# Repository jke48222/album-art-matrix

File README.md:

# Album Art Matrix

A design for an LED wall that shows the cover of whatever song is playing, rendered as a slowly
spinning disc. Nine square LED panels tiled three by three, 480 mm on a side, driven by a Raspberry
Pi 5.

**No hardware has been driven yet.** Not nine panels, not one. This repository is the design, the
circuit simulation, and the software that will run on it. Some of the first light parts have since
been ordered; no panel has arrived. The section below is exact about what exists.

## Building it

[docs/ASSEMBLY.md](docs/ASSEMBLY.md) is the current guide: nine panels are
lit and mapped, and it takes them from the floor to a hung wall. The design
being built is in [design/](design/), the parts and prices at the end of
[PARTS.md](PARTS.md), and [docs/WALL-BUILD.md](docs/WALL-BUILD.md) is the
record of how the wiring was arrived at.

## Status

| Piece | State |
| --- | --- |
| Circuit simulation (`pcb/sims/`) | Done and reproducible. Eight ngspice decks, verified to regenerate their committed outputs bit for bit. |
| Backplane circuit (`pcb/circuit.py`) | Done as a netlist and BOM. 76 components, 105 nets, 345 pin connections. |
| PCB layout (`pcb/backplane.kicad_pcb`) | Routed. 20 design rule check runs are committed as `pcb/drc1.json` through `drc20.json`, and reading them in order is the honest record of the layout. The last run has **no rule violations and no unrouted signal**. What it still reports is 7 ground pour islands: the GND zone fragmented into pieces that no via stitches together, on a board whose entire power argument rests on a continuous return path. Its 107 warnings are 26 silkscreen clearances and, for the rest, KiCad noting that the vendored `pcb/footprints/` are not installed as a system library. |
| Fab outputs (`pcb/fab/`) | Gerbers, drill, pick and place, and board views are exported. **Stitch the ground islands before ordering.** |
| Art pipeline (`brain/art/`) | Built, runs on a laptop, has an offline test. |
| Wall control API (`brain/control.py`) | Built, 335 lines. Serves mode, brightness, spin rate, ambient settings, finishes, ticker and clock text, a sleep fade, a journal with replay, and raw frame and clip pushes on port 8788. Has run on the real Pi and answered the apps over the network; has never had a panel behind it. |
| Display modes (`brain/art/disc.py`, `effects.py`, `text_modes.py`) | Built. Spinning disc, eight ambient light effects (solid, breathe, pulse, rainbow, gradient, plaid, weave, deco), clock and ticker over a generated pixel font, plus pushed frames and clips. All verified as PNGs, none on an LED. |
| iOS companion, first app (`ios-companion/`) | Built, 4,406 lines of Swift. Reads the on device now playing state and pushes it to the reporter, and remote controls the wall. Runs on device. **The simulator cannot exercise it**, because MediaPlayer is stubbed there. Superseded by Tessera for daily use; still installs and works. |
| Tessera (`tessera/`) | The current iOS app. Three designs of the same room (a panel, an iPod with a click wheel, and a rendered room with a record player whose arm follows the song), Studio (draw, photo, words, video on one 64x64 canvas), Archive, Settings with every service set up from the phone, widgets and a Live Activity, an offline outbox, and a stand-in wall the phone runs when no hardware answers. The room's renders come from `tessera/Tools/room/room.py` (Blender, headless). The logo is the Record mark (`RecordMark.swift` and the icon) and the opening is its sting (`StingOpening.swift`: on black, or keyed over the room's light and then the room glitches in from coarse pixels; films `record-sting.mp4` and `record-sting-alpha.mov`, made by `Tools/record_sting.py` and a Higgsfield pass, see `Design/Logos/record/final/README.md`). The Room design is the default. Verified in the simulator against a local brain and installed on a phone; never against a panel. |
| Web app (`web/`) | Built and runs (TanStack Start + React). The whole pipeline reimplemented in TypeScript (Lanczos-3, Pillow-semantics unsharp, gamma 2.2, WB in linear light), plus a seven-source now-playing chain, an LED wall simulator, history, WB profiles, a wiring calculator, and push-to-wall. Verified live against `scripts/mac_reporter.py`; the brain push matches `brain/control.py`'s contract but has not been fired at the real Pi yet. |
| Panel intake QA (`scripts/panel_qa.py`) | Test pattern generator and procedure written, 271 reference frames rendered in `qa_preview/`. `qa/QA-SHEET.md` is an **empty template**. No panel has been through it. |
| Now playing, Apple Music (`brain/nowplaying/applemusic.py`, `applemusic_account.py`, `pushed.py`) | Built. On the Mac: the phone's push, then Music.app, then anything else the Mac plays (next row), then the account view through the MusicKit helper. On the Pi: the phone's push and the account view straight from MusicKit. The phone push and the Mac path have both answered live. |
| Now playing, anything the Mac plays (`brain/nowplaying/macmedia.py`) | Built. Reads macOS's own Now Playing through `media-control`, so Spotify's app, TIDAL, or a browser tab on YouTube Music, SoundCloud or Amazon Music reach the wall with their own artwork, which the reporter serves to the Pi. Verified live on this Mac: a YouTube Music tab reached the reporter with its title, progress and thumbnail, and the brain rendered it. |
| Now playing, Spotify (`brain/nowplaying/spotify.py`) | Built. The app id is pasted in Tessera and handed to the wall, the PKCE sign-in runs on the phone (`tessera://spotify`), and the wall polls from then on. Under the February 2026 rules the app id needs a Premium account, one client ID per developer and five users. **Not linked yet.** |
| Now playing, Last.fm and ListenBrainz (`lastfm.py`, `listenbrainz.py`) | Built. Last.fm needs an API key and a username; ListenBrainz needs only a username. Both are typed in Tessera and kept on the wall. Spotify, Tidal and Deezer report to Last.fm on their own; a browser scrobbler covers YouTube Music, SoundCloud and Amazon Music on a computer. **No account entered yet**, so neither has answered live. |
| Now playing, the wall's ears (`brain/nowplaying/ears.py`) | Built and proven on the Pi 2026-09-14: the USB microphone is read continuously, and when the room is louder than a gate the last few seconds are named through Shazam (shazamio; no key, but an unofficial client that Apple could break). Two six-second clips of quiet music matched in about two seconds each. AcoustID, the first attempt, was removed: it identifies whole files, not a room. Tessera's ears page shows the room's level live with the gate as a mark to drag, what was heard and where in the song, and the Hearing knobs. Handling for a noisy room (a longer clip after each miss, a named song kept through misses, a match with no catalogue record heard twice before it goes up) is built but not yet measured against a TV. |
| HomeKit (`brain/homekit.py`) | Built and running on the Pi 2026-09-15, not yet paired. One bridge: a light (on, off, brightness, a colour for the ambient face), a television (the faces as inputs, the Control Centre remote's keys), an occupancy sensor (sound in the room) and a motion sensor (music on the wall). The wall draws its pairing QR on the panel while unpaired; `GET /homekit` has the code as text. Siri, the Watch and scenes need nothing else; automations and a HomePod need a home hub. |
| Vinyl scrobbling (`brain/scrobble.py`) | Built 2026-09-15, running on the Pi, waiting for the ListenBrainz user token from the phone's ListenBrainz page. Every record the ear names is posted as playing-now, then as a listen after half the song or four minutes; held-through-noise and heard-again-within-the-song count once; listens the network refused wait in `scrobbles.jsonl` and go later in batches. Fifteen offline tests in `brain/tests/test_scrobble.py`. |
| Knock twice (`brain/nowplaying/knock.py`) | Built 2026-09-15, on the Pi, waiting for a session of real knocks to set the numbers. Two knocks on the frame, alone, toggle the wall between off and the face it had; a whistle bending up or down does the same for a frame that does not carry a knock. Both run on the ear's own chunks, log every candidate with its numbers, and are Hearing knobs on the phone. Fourteen offline tests. |
| Teach the wall a song (`brain/nowplaying/teach.py`) | Built 2026-09-15, on the Pi. The wall's own landmark fingerprint library (numpy, the Shazam idea; Olaf needs Zig, which the Pi's Debian lacks), asked before Shazam. It learns a song's iTunes preview when another source names it and the ear keeps missing it, learns the room's own hearing of a song after fifteen loud seconds, and learns by name through `POST /teach/learn`. Three Hearing knobs, a Taught songs group on the phone, nine offline tests including a clip heard through a room. |
| The wall's own ears, the voice (`brain/voice/`, `docs/VOICE.md`) | Built 2026-09-15. A wake word on the ear's stream, chosen on the phone from openWakeWord's Hey Jarvis, Hey Mycroft, Hey Marvin and Alexa, or a phrase of your own taught by saying it to the wall six times (matched on the same speech embeddings with the room's sound taken out; measured on synthetic voices, it heard 97% of new voices in an echoing room with no false wakes in 3.6 minutes of talk). Each word keeps its own sensitivity, with a live meter on the Voice page. Then the Horizon face while it listens, speech to text on the Pi (faster-whisper tiny, about a second and a half a sentence), a grammar of commands done with no cloud, and Claude for the rest. `GET /voice`, `GET /voice/meter`, `POST /voice/wakeword`, `POST /voice/enroll`, `POST /voice/wake` and `POST /voice/say` for testing without a microphone. |
| Ask the wall (`brain/ask.py`) | Built 2026-09-15, waiting for the Claude key from the phone's Services page. A question by voice or `POST /ask` goes to Claude Opus 5 with the wall's own tools (what is playing, the journal, the face, brightness, a timer) and comes back as words on the panel, paged, 1x at 64 and 2x at 192. A Siri Shortcut recipe is in `docs/ASK.md`. |
| Leave a note (`POST /note`, `docs/ASK.md`) | Built 2026-09-15. "Hey Siri, tell the wall back at six" runs the words across the panel for a while, then the wall goes back to what it was doing. Also a voice command. |
| Show me, play me, the earworm finder (`brain/show.py`) | Built 2026-09-15, pictures 2026-09-22. A picture of a thing by name (Google Images with a key and search engine set under Services, otherwise the web through DuckDuckGo's image search, then the lead image of its Wikipedia page, then Openverse) or a cover by name from iTunes into the frame face, a video by name through yt-dlp into the video face, and a song from the words remembered through Claude, with its sleeve. Plain words mean a picture unless they name a record the wall has worn or shelved; "cover", "album", "by" ask for a sleeve, "a picture of" asks for a picture. By voice or `POST /show` (with `kind`: picture, cover or any), `/play`, `/earworm`. |
| Weather faces (`brain/weather.py`, `brain/art/weather.py`) | Built 2026-09-15 and redrawn the same day at full fidelity, proven on the Pi with the real forecast for the room's place. A face that is the weather: a sky the colour of the hour (blue at noon, warm at the horizon at dawn and dusk, deep at night with stars that twinkle), rolling hills in silhouette, a sun with a halo and slow rays on its real arc, the moon with tonight's phase and its seas, clouds as stacked puffs with lit tops and shaded bases in two layers that drift, rain that leans with the wind and splashes on the ground, drizzle finer, showers that come and go, snow in two sizes banking up on the hills, fog as soft banks of haze drifting through, thunder with a forked bolt and a flash that fades; the temperature outlined so it reads over anything, at 192 the high and low, the next six hours and sunrise and sunset ticks where the arc meets the hills. Everything still for the hour is drawn once and kept. Every WMO code has a scene. Open-Meteo, no key; a place named once on the phone's Weather page, which is a card now: the wall's live frame, the temperature large, the sky in words, the day's range, feels, wind, sunrise, sunset and the next six hours. Seven tests. |
| The shelf (`brain/shelf.py`, `brain/art/mark.py`) | Built 2026-09-15, on the Pi, waiting for a Discogs token and username (Services > Discogs). The wall reads the collection's main folder every six hours, paced under Discogs's limit, and keeps it in `shelf.json`. A song from an album on the shelf gets a small record in the sleeve's corner, 5 px at 64 and 11 px at 192, dark on a light corner and light on a dark one, on every face that shows the sleeve; the Shelf knob turns it off. The pressing (year, label, catalogue number, country, the lowest price copies are going for) goes to the phone as `owned` and shows under the song; the price is fetched on a worker and cached a day. The Discogs page lists the shelf with plays per release from the journal. Matching folds case, accents, brackets, feat., Discogs's (2) and Deluxe tails, takes near titles (Blonde, Blond) and any listed artist, and prefers the vinyl. Seven tests over forty tricky releases. |
| Posters (`brain/posters.py`) | Built 2026-09-15, on the Pi, waiting for a TMDB key (Services > Posters) and for the Mac's reporter to be restarted from this tree. A show or a film in a browser on the Mac used to be dropped by the reporter (a browser icon is not a sleeve); now its name rides on the empty answer as an `X-Mac-Show` header, a brain that does not know about shows sees nothing new, and this brain looks the name up on The Movie Database, television first, then films. The poster is the sleeve, cut square from a little above the middle rather than squashed (`brain/art/pipeline.py` `square`, which now guards every non-square picture), the answer is playing with art, the journal marks it `kind: show`. Hits kept a month, misses a day, in `posters.json`. Six tests. |
| Imagine (`brain/imagine.py`) | Built 2026-09-15, drawing on the Pi with his OpenAI key. "Create a purple elephant", by voice or from the Imagine page: Claude rewrites the words as a prompt for one large, lit, textured, believable subject with no text; the newest OpenAI image model the key can reach draws it (gpt-image-2, then 1.5, then 1, with a fallback on a missing model) at medium quality to start (a good picture in well under a minute: 54 s for a lighthouse on gpt-image-2; high is the most detailed and takes minutes), or Google's Imagen Ultra. OpenAI streams three partial images and the wall shows the picture being drawn: the moment the words arrive it goes into its imagine face, a soft band of light sweeps across while the model thinks, each partial crossfades in as it lands, a line at the foot counts them, and the finished picture is held for ten minutes. Every image is brought to the wall's size in linear light with a gentle stretch. Kept at full size with its words in `imagined/`; `GET /imagine` lists them with the live state, `GET /imagine/<id>.png` serves one, `POST /imagine/show` puts one back with a quick reveal. AI pictionary shows its sketch forming the same way. The Imagine page shows the drawing live; Services > Images chooses the drawer and the quality. Ten tests. |
| AirPlay to the wall (`brain/nowplaying/airplay.py`, `brain/nowplaying/receiver.py`, `docs/AIRPLAY.md`) | Done 2026-09-15. The wall is an AirPlay speaker called Wall. `pi/install-airplay.sh` unpacks Debian's shairport-sync, a classic AirPlay build, so there is no nqptp and no root; the brain runs it with a config of its own, starts it again when it stops, restarts it when the phone renames it, and stops it with itself. A reader on its metadata pipe takes the title, artist, album, length, artwork, position, pause, resume, end and the sender, and answers right after the phone in the chain; a song that comes without artwork gets its sleeve by name. On the phone: whether it is receiving and from what, a switch, and the name. Proven on the Pi with an Apple device playing to it. Grouping with HomePods in the Home app needs AirPlay 2, which needs sudo. |
| Games shell and Wordle (`brain/games/`) | Built 2026-09-15 and played on the Pi over HTTP and by a spoken guess. One game at a time, held by the GameHost: mode `game`, the wall the board and the phone the hand; `GET /game/list`, `GET /game`, `POST /game/start`, `/game/move`, `/game/hear`, `/game/end`; every change bumps a sequence the phone polls; played, won, streak and best per player per game in `games.json`; a scoreboard face between games. Words heard by the wall's ears go to the running game before the command grammar. `brain/games/board.py` draws the same board at 64 and 192 from one description (tiles, grids, the 5x7 font at 1x and 3x). Word lists built from a public frequency list through the system dictionary: 30,000 common words, 2,400 five-letter answers, 8,500 valid guesses. Wordle: six guesses, the repeated-letter rule, a refused non-word does not count, the keyboard state for the phone, up to four players taking turns. Four tests. The phone's Games screen is next. |
| Sudoku, Spelling Bee, Letter Boxed, Connections (`brain/games/`) | Built 2026-09-15, each shown on the Pi. Sudoku: a full grid by randomised backtracking, digits removed while a counting solver still finds one solution, rated by the guesses that solver needs; easy, medium or hard; touch on the phone or "row three column four is seven"; wrong digits red. Spelling Bee: a hive from a common seven-letter pangram, the centre chosen to keep the most words, ranks from Beginner to Genius, Queen Bee for every word. Letter Boxed: two chaining common words that use twelve distinct letters and lay out on four sides with no two in a row from one side, kept as the par; the wall draws every word's lines. Connections: Claude writes a set (structured output) or one of eight bundled sets, yellow to purple, one away, four mistakes; say four words or tap four tiles. Fourteen tests. |
| Strands, mini crossword, Contexto, sliding puzzle, cover reveal, reaction knock, whistle bird (`brain/games/`) | Built 2026-09-15, each shown on the Pi. Strands: a themed set from Claude (structured output, forty-eight letters checked) or six bundled, threaded through the 6x8 grid by cutting a random whole-grid path (backbite moves on a serpentine) into the words, the spangram made to touch two sides; extras earn hints. Mini crossword: symmetric patterns filled from the common words most-constrained-slot first, Claude clues or a hand-clued puzzle, entered by voice ("one across is lamp") or a letter at a time, a check that marks wrongs red. Contexto: ranks by cosine on twenty thousand GloVe vectors cut to a 1.9 MB file, green under 300, the rank in big digits with a log bar. Sliding puzzle and cover reveal on a sleeve from the journal: a scramble by legal slides, blocks tapped or "up, down, left, right"; a Gaussian blur that sharpens over thirty seconds, first to name the album or artist. Reaction knock: red, green, the milliseconds on the panel, timed on the ear's own clock, false starts caught, phone taps allowed. Whistle bird: the ear's pitch, the whistler's range learnt in the first notes, pipes, a score. The ear now hands every lone knock, double, whistle and pitch to the running game first, so nothing switches the wall off mid-game. Twenty-three tests. |
| Heardle, pub quiz, twenty questions, AI pictionary, the arcade (`brain/games/`) | Built 2026-09-15. Heardle: a journal song with an iTunes preview the phone plays for one, two, four, seven, eleven, sixteen seconds as guesses miss or skip; the wall's six bars and a needle; the sleeve on the reveal. Pub quiz: a Claude round (structured output) or two bundled, twenty seconds a question, one answer per player, folded matching against every acceptable answer, scores on the wall. Twenty questions: Claude asks from the whole history and guesses when sure; a knock is yes, a whistle no; twenty and you win. AI pictionary: the image drawer draws a secret word from a list of drawable things with no text, sixty seconds to name it. The arcade: Pong (phones as paddles, the wall plays the other side alone, first to seven), Snake (a 32-cell grid, the phone the remote, or say the direction) and Tetris (a seven-piece bag, wall kicks, a ghost, levels). Eleven tests; the arcade shown on the Pi. |
| The Games sheet on the phone (`tessera/Tessera/Games.swift`, `GamesBoards.swift`, `GamesPlay.swift`) | Built 2026-09-15 and installed. A Games tile among the faces opens a sheet: the games the wall knows, your name for the scoreboard, the one that is on, its scores. Every game has its own screen polling the wall once a second and redrawing on its sequence: Wordle's rows and keyboard, Sudoku's grid and digit pad, Connections' tiles, the Spelling Bee hive, the Letter Boxed square, Strands traced by a finger, the mini crossword with its clues, Contexto's ranked list, Heardle playing the clip for the seconds allowed, the sliding blocks tapped over the wall's own frame, the reaction button, the whistle bird's slider, twenty questions' yes and no, the quiz card, pictionary's clock, Pong on the phone's tilt, Snake and Tetris on a remote and swipes. Words are typed or spoken to the phone's own recogniser, primed with the game's words. The state comes as JSON any game can shape. |
| The boards' design (`brain/games/board.py`, `scripts/render_games.py`) | Redrawn 2026-09-15 on one kit: a restrained palette, tiles with a lit top edge and a shaded bottom at 192 and their corners off at both sizes, hexagons, thick lines and arcs, soft glows, easing, a header band with a coloured mark at 192, a banner for the end of a game, a scoreboard with bars. Wordle's rows flip in a tile at a time, Connections shakes on a miss, Contexto pops its rank in, the quiz counts down on a ring, the reaction field breathes, the whistle bird flaps under stars, Pong's ball leaves a trail, Tetris has bevels, a ghost and a next piece. `scripts/render_games.py` draws every board at both sizes as one contact sheet. The phone's Games sheet has a hero card with the wall's live frame, a motif for every game in its colour, the scores as bars, and a live strip of the wall over each board. |
| Every feature in its place (`tessera/Tessera/Features.swift`, `brain/homekit.py`, `brain/art/horizon.py`, `brain/art/answer.py`) | 2026-09-15. Settings has a "What the wall can do" list: Ask the wall (a question typed, the answer on the panel or here, the last dozen), Notes (words on the panel for a set time, with what is up now), Show me (a cover or a video by name), Earworm (the words you remember, the sleeve with the name along its foot), Imagine, Weather, Games, Voice (the wake word and speech, listen now, say it from here, the last heard), HomeKit (pairing, the setup code on the panel, the remote's inputs), The shelf (the records as covers, most played first), Teach the wall (a song by name, the library). The HomeKit remote has every face as an input, the weather, the games and the last picture drawn among them; its arrows and select play a game that is on, back puts it down, play and pause switch the wall off and on. The listening line ripples along its length with the voice and glows under it; the thinking bead trails light; answers type themselves out with a cursor. An organisation-level Claude key now works: the wall sends the workspace id set beside it. |
| Service settings from the phone (`brain/services.py`, `tessera/Tessera/Services.swift`) | Built and exercised against a brain on the Mac: every key and username above is set from Tessera's Services pages, kept in `services.json` on the wall, and applied to the running adapters without a restart. No config file is edited by hand once the wall is deployed. |
| Video on the wall (`brain/video/`, `tessera/Tessera/Video.swift`, `VIDEO.md`) | Built and exercised on the Pi 2026-09-06. A YouTube link (or any link ffmpeg reads) pasted in Tessera's Video face: the wall resolves it the way the YouTube iPhone app does, streams the 144p picture through ffmpeg to 64 px at 15 fps (a third of a second of CPU per twenty seconds of video, about 26 MB of frames), and downloads the sound in ranged pieces for the phone to play; the phone's player is the clock. First frame in about a second, sound ready in under two. No new binaries on the Pi. Share-sheet target (`tessera/TesseraShare/`): from YouTube, Safari or Photos, Share, then Tessera; a library video is sent up as a small H.264 picture (`POST /video/upload`) and the phone plays its own sound. Videos behind YouTube's signed-in token (big label releases) stop after the first megabyte from every client identity the wall asks; those fall through to **yt-dlp** (`brain/video/ytdlp.py`, installed by `pi/install-ytdlp.sh`), which fetches them itself into the RAM disk. Verified on the Mac 2026-09-06: the refused video plays, ready in 7.3 s against 1.8 s for the fast path. No JavaScript runtime installed; not needed by the client yt-dlp uses. |
| Renderer (`renderer/art_display.c`) | 202 lines of C. Compiled and run on the Pi 5; frames flow through the FIFO and the map-rate cap. It has never had a panel on the other side. |
| Pi provisioning (`pi/`) | Executed on the real Pi: bootstrap, venv, renderer build, systemd units for brain and renderer. The wall boots headless and answers the network. |
| Parts | **Panels arrived**: ten Waveshare P2.5 64x64, driver confirmed FM6124HJ (conventional, no init sequence needed). Pi 5, card, cooler and sundries on hand. First light is blocked on the HUB75 bonnet and 5V supplies still on order. `PARTS-TRACKER.xlsx` carries prices actually paid; `PARTS.md` remains the list. |
| White balance gains | Placeholders. `config.example.toml` labels the current values "a GUESS" pending measurement. |

Everything above is design, simulation, and software. Nothing in this repository has met a panel,
and that is the only claim that matters until it changes.

## What problem this solves

Music has a cover, and almost nobody looks at it any more. It lives in a thumbnail the size of a
postage stamp, at the corner of a phone that is in a pocket. The cover is the one piece of visual art
that shipped with the record, and the streaming era has quietly retired it.

An LED matrix wall puts it back on the wall at the size it deserves, and makes it live: it changes
when the song changes, without anyone touching anything.

The obvious approach, a cheap TV showing a full screen image, fails for a specific reason. A TV in a
room reads as a switched-on screen. It has a bezel, a backlight glow, an off state that is a grey
rectangle. An LED matrix behind a diffuser reads as an object that emits light, closer to a lamp or a
sign than a display, and its off state is genuinely black. That difference is the entire point of
building the hard version.

## What HUB75 is

HUB75 is the de facto wiring standard for chainable RGB LED matrix panels. A 16 pin ribbon carries
six colour data lines (two sets of red, green, blue, because the panel drives two rows at once), five
row address lines named A through E, a clock, a latch, and an output enable.

The important thing about HUB75 is what it does **not** have: memory, or brightness control, or any
intelligence at all. The panel is a shift register attached to LEDs. It displays exactly one row pair
at a time, and it stays lit only for as long as you hold output enable low. To make a picture, the
host has to scan every row of the panel, over and over, fast enough that persistence of vision fuses
the rows into an image, and it has to modulate the on time of each row to produce anything other than
full brightness. If the host stops, the image does not freeze. It goes dark.

That is why this project needs a real time thread pinned to a dedicated CPU core, and why the signal
integrity of a 25 MHz clock down a ribbon cable is a design problem rather than a detail.

## How it works

```
  Mac                          Pi 5
  ---                          ----
  Music.app ---+
               +--> mac_reporter.py --HTTP--> brain/main.py
  MusicKit  ---+   (port 8787)                     |
  helper                                           | poll, detect track change
                                                   v
                                          art/fetch.py
                                          cover URL to cached image
                                                   |
                                                   v
                                          art/pipeline.py
                                          Lanczos downscale, unsharp, sRGB to
                                          linear, white balance, re-encode
                                                   |
                                                   v
                                          sinks/pi_renderer.py
                                          one RGB888 frame per open/write/close
                                                   |
                                                   v
                                          /tmp/album-frame.fifo  (named pipe)
                                                   |
                                                   v
                                          renderer/art_display  (C daemon)
                                          reader thread, plus a refresh thread
                                          pinned to isolated CPU 3
                                                   |
                                                   v
                                          HUB75 ribbon --> LED panels
```

The seam worth noticing is the named pipe. The brain and the renderer are separate processes that
share nothing but a byte stream of raw pixels, so either can be restarted, replaced, or run under a
debugger without the other caring. `art_display` re-opens the pipe on end of file and keeps showing
the last frame it received, so a crashed or upgraded brain leaves the wall lit rather than black.

On a laptop, `sinks/mac_preview.py` swaps in for the pipe and writes a scaled up PNG with a pixel
grid instead. That is how the whole image path was developed with no panel in the room.

## The simulations

This is the part of the project that is fully substantiated, and it is the part worth reading.

`pcb/sims/run_sims.py` writes ngspice decks, shells out to `ngspice -b`, and plots the results. Five
deck templates produce eight numeric output files and three figures, all committed. I re-ran all
eight decks from the committed `.cir` files and compared against the committed `.txt` outputs: every
one matches bit for bit, so the numbers below are reproducible rather than remembered.

Read them as circuit models, not as measurements. Nothing here has been checked against a real board,
because there is no real board.

### Why HUB75 lines need series termination

A logic driver puts out a fast edge. A 30 cm ribbon cable is not a wire, it is a transmission line
with inductance and capacitance distributed along it, and the panel at the far end is a high
impedance input that reflects almost all of the energy that arrives back toward the driver. The
reflection returns, bounces off the driver, and comes back again. What you see at the panel is
ringing: the voltage overshoots well past the supply rail, undershoots below ground, and settles only
after several round trips.

Series termination is the cheap fix. Put a resistor in line at the driver so that the driver's output
impedance plus the resistor roughly matches the cable's characteristic impedance. The reflection that
comes back is then absorbed instead of re-launched.

The sweep drives a 25 MHz pulse through an 18 ohm source resistance and a six section lumped LC
ladder standing in for the ribbon (25 nH and 2.5 pF per section), into an 18 pF panel input.

| Series resistor | Peak at panel input | Worst undershoot |
| --- | --- | --- |
| 0.1 ohm (effectively none) | 8.71 V | -4.11 V |
| 22 ohm | 7.09 V | -2.13 V |
| **33 ohm** | **6.48 V** | **-1.49 V** |
| 47 ohm | 5.86 V | -0.86 V |

Undamped, a 5 V signal swings to 8.7 V and to -4.1 V. Those excursions are what the panel driver
chip's input protection diodes have to eat, on every clock edge, forever.

47 ohm damps hardest, but it also slows the edge, and at 25 MHz the edge is a large fraction of the
bit period. 33 ohm is the value in `pcb/DESIGN.md`, chosen from this sweep as the point where
overshoot is tamed without blunting the edge. One caveat this figure carries in its own legend: the
plot says "Rs = 0" for the first trace because the script formats the label with `int(rs)`, while the
deck actually uses 0.1 ohm.

### What IR drop costs across the power distribution

An LED panel at full white is a serious load. One 64 by 64 P2.5 panel pulls roughly 4 A, so a section
of three panels pulls about 12 A. Copper has resistance, and 12 A through even a short run of 14 AWG
wire, a fuse, fuse clips, and a panel harness adds up to a voltage that is missing by the time it
reaches the panel. That is IR drop: current times resistance, the voltage the wiring keeps for
itself.

It matters because these panels are not tolerant. Below roughly 4.9 V the driver chips start
misbehaving, and the symptom is not a clean failure. It is dim patches, colour shifts on bright
frames, and flickering that only appears on white heavy album covers.

The deck is a DC sweep of the supply's output trim, with three constant current loads of 4 A each,
through modelled trunk wire, 7 milliohm of fuse and clips, and 0.4 m of 18 AWG harness per panel.

| Trunk length | Panel voltage at 5.00 V trim | Trim needed for 5.00 V at the panel |
| --- | --- | --- |
| 1.0 m of 14 AWG | 4.71 V | about 5.30 V |
| 0.5 m of 14 AWG | 4.81 V | about 5.20 V |

So a supply set to a perfect 5.00 V delivers 4.71 V to the panel, below the floor, and the wall
misbehaves on bright frames for reasons that look like a software bug. The answer is not thicker wire
alone, it is to trim the supply up so the panel lands in range, and the sweep says exactly how far.
Halving the trunk length is worth 0.10 V, which is why the design splits the wall into three
independent 12 A sections instead of running one 36 A trunk.

### Why inrush limiting matters

A switching power supply has a large capacitor across its input. At the instant you plug it in, that
capacitor is empty, and an empty capacitor looks like a short circuit. The only thing limiting the
current is the resistance of the mains wiring and the capacitor's own equivalent series resistance,
which together are a fraction of an ohm.

The deck models the first few AC cycles into roughly 560 uF of input bulk, at the worst case moment
of connection (the peak of the mains sine wave).

| Configuration | Peak line current |
| --- | --- |
| No limiter | 275 A |
| SL22 NTC thermistor, 10 ohm cold | 15.8 A |

275 A is a number that trips breakers, welds switch contacts, and shortens the life of everything it
passes through. The fix is a negative temperature coefficient thermistor in the mains line: cold, it
is 10 ohm and limits the surge to 16 A, and then it self heats within a second or two down to a
fraction of an ohm so it costs almost nothing during normal running. This is why an SL22 10005 is on
the Mouser line of `PARTS.md` and why the design puts it in the AC line rather than anywhere on the
board.

The model uses a generic diode bridge and a fixed cold resistance with no self heating, so it is
honest about the first cycle and says nothing about the settled behaviour.

## The board, written as a Python program

`pcb/circuit.py` is 207 lines that describe the backplane as data and emit it. Running it prints a
connectivity report and writes `backplane.net` (a KiCad netlist) and `bom.csv`. I ran it into a
scratch directory and diffed: both outputs regenerate identically to the committed files.

```
parts: 76   nets: 105   pin connections: 345
single-node nets (should be none): none
GPIOs consumed: [2, 3, 4, ..., 27]
```

The reason to do it this way instead of drawing a schematic is that most of this board is repetition
with an index. Three chains, nine panel drops, three power sections, twenty six buffered GPIO lines
each needing a series resistor from a shared pool of arrays. In a schematic editor that is a lot of
careful copying, and copying is where wiring errors come from. As a loop it is four lines, and the
pin map is stated once:

```python
SHARED = {"CLK": 17, "LAT": 4, "OE": 18, "A": 22, "B": 23, "C": 24, "D": 25, "E": 15}
CHAIN = {1: {"R1": 11, "G1": 27, "B1": 7, "R2": 8, "G2": 9, "B2": 10}, ...}
```

The script also checks itself. It reports any net with fewer than two nodes, which catches the most
common data entry mistake (a pin connected to nothing), and it prints which GPIOs the design consumes
so the fact that this pinout uses every one of BCM 2 through 27 is visible rather than discovered
later.

What this is not: a board. A netlist says what connects to what. It says nothing about whether the
parts fit in 170 by 110 mm, whether the 12 A pours are wide enough, or whether the layout passes a
manufacturer's design rules. That work is listed as the next step at the bottom of `pcb/DESIGN.md`
and has not been done.

## The render path

`renderer/art_display.c` creates the named pipe, holds it open, and streams frames out of it back
to back. It does not hand the brain's bytes to the panel library as they are: it keeps the last frame
received and, once per scanned frame, draws it again with temporal dithering, a running fraction per
LED colour, so a pixel can show a fraction of one of the library's 64 brightness slots and a dark
brown stops breaking into a lone red LED. The library bakes its brightness cap into a table once at
launch, so the renderer applies the cap itself, live, from each frame's header. It maps exactly once
per scanned frame by waiting on a swap counter that `pi/hub75-swap-counter.py` adds to the library;
before that counter the safe rate was 60 Hz and anything faster tore. The main thread calls
`render_forever()`, which owns the refresh loop.

It compiles and runs on the Pi 5. It includes `<rpihub75/rpihub75.h>` and links `-lrpihub75_gpu`,
the third party library `bitslip6/rpi-gpu-hub75-matrix`, which `pi/bootstrap.sh` clones and builds;
that has all run on the real Pi. What has not happened is a panel: the renderer's output has only
ever gone into the library, never into LEDs.

One number needs a label. The comment in `art_display.c` and the comment in `pi/run_renderer.sh` both
mention 9600 Hz. **That is the refresh rate advertised by that third party library, on hardware this
project does not own.** It is a design target that motivates the architecture (a refresh that fast is
what makes the wall photograph without banding, and what makes a torn frame invisible), and it is not
a measurement. Nothing in this repository has measured a refresh rate.

Likewise, `pi/run_renderer.sh` passes `-p 1 -c 1 -x 64 -y 64`: one port, one chain, one 64 by 64
panel. `config.example.toml` says the same thing in a comment: "S1: one 64x64 P2.5 panel. Later: 128
(4 panels) / 192 (9)". The nine panel wall is the plan. The configured system is one panel.

## CPU isolation

`pi/bootstrap.sh` appends `isolcpus=3 nohz_full=3` to the Pi's kernel command line. Two settings,
both about getting the Linux scheduler out of the way:

- `isolcpus=3` removes core 3 from the scheduler's general pool. Ordinary threads will not be placed
  there, so a thread that pins itself to core 3 has the core to itself.
- `nohz_full=3` stops the periodic timer interrupt on that core when only one thread is runnable on
  it. Without it, the kernel interrupts the core hundreds of times a second just to keep time.

The reason this is worth doing is in how HUB75 works, above. The refresh thread is not rendering
frames, it is bit banging a scan: hold a row's data on the bus, pulse the clock, latch, hold output
enable low for a precisely timed interval, repeat. The interval is what encodes brightness. If the
scheduler preempts that thread mid interval, the row stays lit longer than intended, and the result
is a visible bright line or a flicker in what should be a still image. A dropped frame in a video
game is a stutter you forgive. A late microsecond here is a defect on a wall you are staring at.

This is configured, not demonstrated. The line is in the script, the script has never run, and no
latency has been measured.

## Colour, and the number that is still a guess

The pipeline in `brain/art/pipeline.py` does white balance the correct way, which is the one part of
the image path with a real argument behind it.

RGB LED panels are not neutral. Their green and blue emitters are typically far more efficient than
their red, so a frame that says "white" comes out cyan. The correction is per channel gains. The
subtlety is *where* you apply them: an 8 bit image is gamma encoded, not linear, so scaling those
values directly scales perceptual codes rather than light. The pipeline decodes to linear light
(gamma 2.2), applies the gains there, clips, and re-encodes:

```python
linear = np.power(arr, 2.2)
linear *= np.asarray(gains, dtype=np.float32)[None, None, :]
np.clip(linear, 0.0, 1.0, out=linear)
encoded = np.power(linear, 1.0 / 2.2) * 255.0
```

The gains themselves are R 1.00, G 0.75, B 0.55, and `config.example.toml` labels them exactly as
they should be labelled:

> these starting gains are the research's typical values, a GUESS.

They are a starting point from published typical values, not a measurement of any panel. Measuring
them is a written procedure that has not been carried out: `scripts/WB-PROCEDURE.md` calls for a
TCS34725 colour sensor on a Pico 2 W (`scripts/pico_colorimeter.py`) held against a panel showing
full white (`scripts/show_white.py`), after a ten minute warm up because LED output shifts as the
panel heats.

## Running the software with no hardware

Requires Python 3.11 or newer (the config loader uses `tomllib`).

```bash
python3 -m venv .venv
.venv/bin/pip install -r brain/requirements.txt   # requests, Pillow, numpy
cp config.example.toml config.toml
```

The offline test needs no network, no accounts, and no panel. It synthesizes a 640 by 640 cover
containing a smooth gradient, a disc, and fine detail, chosen to expose banding, aliasing, and
downscale mush respectively, then runs the full art pipeline:

```bash
.venv/bin/python scripts/smoke_test.py
```

A successful run prints `smoke test OK:` and writes three files:

| File | What it shows |
| --- | --- |
| `preview_out/smoke_source.png` | The synthetic source cover |
| `preview_out/panel.png` | 64 by 64, scaled up with hard pixel edges and a grid, as the wall would show it |
| `preview_out/wb_compare.png` | Side by side, without and with the white balance step |

`wb_compare.png` will look wrong on a monitor, and that is the point. White balance compensates for
panel hardware, so on a correctly behaved screen the corrected version looks orange.

To run the live loop against Apple Music on a Mac:

```bash
.venv/bin/python -m brain.main --config config.toml
```

It polls every 5 seconds and rewrites `preview_out/panel.png` on each track change. Two caveats. The
Apple Music adapter's highest tier shells out to a MusicKit helper at
`~/.config/widgetsuite/musickit-fetch.py`, which lives outside this repository and is not verified
here; its lower tier uses `osascript` against Music.app, which triggers a one time macOS automation
prompt. Add `--once` to poll a single time and exit.

To have the Mac report every other app it plays as well (Spotify's app, TIDAL, a browser tab on
YouTube Music), install `media-control` once; both the brain on a Mac and `scripts/mac_reporter.py`
pick it up on their next start, with no setting to flip:

```bash
brew install media-control
```

Connecting a service needs no computer at all. Tessera's Settings > Services pages take the Spotify
app id, the Last.fm key and username and the ListenBrainz username, hand them to
the wall (`POST /services`), and the wall keeps them in `~/.config/album-art-matrix/services.json`
and starts using them at once. The Spotify sign-in itself runs on the phone. The values in
`config.toml` are only seeds; anything set from the phone wins. What still needs a computer is the
one-time `./deploy.sh` that puts the software on the Pi.

The developer's own keys live in `tessera/Tessera/DeveloperKeys.swift`. Only what is safe to
publish goes in there, because this repository is public. The Spotify app id qualifies: it is public
by design, the way every app with a "Sign in with Spotify" button was registered once by its
developer, and the sign-in uses PKCE so there is no secret to keep. A **Last.fm API key does not**:
it is bound to the developer's Last.fm account and a published one can be copied and revoked for
someone else's abuse, so that field is empty and the key is typed into Tessera's Services page
instead, which keeps it in `services.json` on the wall. With a key filled in, the app hands it to
any wall it meets that is missing one, and a person only ever signs in to Spotify or types a
Last.fm or ListenBrainz username. With it empty, the Services pages walk through making it by hand.

To re-run the circuit simulations, you need `ngspice` on your PATH plus numpy and matplotlib:

```bash
python3 pcb/sims/run_sims.py    # rewrites the .txt data and the three PNGs
python3 pcb/circuit.py          # rewrites backplane.net and bom.csv
```

## First light, when the parts arrive

The order of operations in `pi/PI-SETUP.md`, which is a runbook whose third step literally begins
"Pi arrives". Nothing below has been done.

1. Flash Raspberry Pi OS Lite 64 bit, hostname `album-matrix`, user `pi`, SSH key configured.
2. `./deploy.sh --bootstrap`, which rsyncs the source and remotely runs `pi/bootstrap.sh`: apt
   dependencies, zram, clone and build the panel library, append the CPU isolation flags, build the
   renderer, create the venv, install the systemd unit (not enabled).
3. Reboot, so the kernel command line change takes effect.
4. Wire it with everything unplugged. Ribbon into the panel's INPUT connector, panel power from its
   own supply, never from the Pi. Mains into the supply last.
5. Start `pi/run_renderer.sh` in one shell and the brain in another, with `[sink] type = "pi"` and
   the reporter endpoint pointed at the Mac.
6. Warm up ten minutes, then run the white balance procedure and replace the guessed gains with
   measured ones.

The first honest checkpoint is the one `pi/PI-SETUP.md` names: a photograph of the panel next to the
same cover on a phone, with the two colours matching. Until that photo exists, this project has not
displayed anything.

## Project layout

```
brain/                  4238 lines of Python: the now playing control plane
├── main.py             Poll loop, render loop, journal writes. A dirty event
│                       from the API wakes it instead of waiting out the poll.
├── services.py         Keys and usernames the phone hands the wall; kept in
│                       services.json, applied to the adapters live
├── control.py          HTTP state API on 8788. Mode, brightness, spin rate,
│                       ambient, finishes, ticker and clock, sleep fade,
│                       journal + replay, raw frame and clip pushes. State
│                       persists to control.json; plays go to journal.jsonl.
├── nowplaying/
│   ├── pushed.py       What the phone posts straight to the wall
│   ├── applemusic.py   Tiered: a state file, Music.app over osascript, any
│   │                   other app the Mac plays (macmedia), the account view
│   ├── applemusic_account.py  The account view from the Pi, no Mac in the path
│   ├── macmedia.py     macOS Now Playing via media-control: Spotify's app,
│   │                   TIDAL, browser tabs, with their artwork
│   ├── spotify.py      PKCE OAuth from the phone or a Mac; the wall polls
│   ├── lastfm.py       One account Spotify, Tidal and Deezer report to
│   ├── listenbrainz.py The open ledger; reading it needs no key
│   └── ears.py         The wall's microphone, read all the time; Shazam names it
├── art/
│   ├── fetch.py        Cover URL to cached image (decode before cache)
│   ├── pipeline.py     The colour work
│   ├── disc.py         Sleeve as a spinning disc, supersampled, fixed sheen
│   ├── effects.py      Eight ambient generators for when nothing is playing
│   ├── pixelfont.py    The 5x7 font, single source for both apps' Swift copies
│   └── text_modes.py   Clock and scrolling ticker over that font
└── sinks/              mac_preview.py (PNG, for development), pi_renderer.py (FIFO)

ios-companion/          AlbumWall, the first app, 4,406 lines of Swift
├── AlbumWall/          The app: on device now playing push, wall remote,
│                       photo and video push, App Intents, Live Activity
├── AlbumWallWidgets/   Home screen widgets and the Live Activity surface
└── design/             Screen designs the app was built from

tessera/                The current iOS app, 26,472 lines of Swift
├── Tessera/            Wall screen, Studio (draw / photo / words / video),
│                       Archive, Settings, offline outbox, stand-in wall
├── TesseraWidgets/     Home screen widgets
├── Shared/             Live Activity attributes, shared snapshot
└── Tools/              gen_pixelfont.py (regenerates both apps' fonts),
                        make_icon.py

web/                    The control plane in a browser: pipeline (same math,
                        TypeScript), source chain, wall simulator, history,
                        WB profiles, power model, push to the Pi brain.
                        `cd web && npm install && npm run dev`. See web/README.md.

pcb/
├── DESIGN.md           The backplane's rationale, signal design, power design, costs
├── circuit.py          The circuit as data. Emits the two files below.
├── backplane.net       Generated KiCad netlist, 76 parts, 105 nets
├── bom.csv             Generated bill of materials
├── layout.py           Placement, driving the KiCad board file
├── backplane.kicad_pcb The board. Routed; 7 ground pour islands left to stitch.
├── drc*.json           20 design rule check runs, in order. The trend is the story.
├── footprints/         Vendored .kicad_mod files, so the board opens anywhere
├── fab/                Gerbers, drill, pick and place, board views
└── sims/               ngspice decks, numeric outputs, three figures, run_sims.py

renderer/               art_display.c (202 lines) and its Makefile. Builds and
                        runs on the Pi; no panel has been on the other side.
pi/                     PI-SETUP.md runbook, wiring.svg, bootstrap.sh, run_renderer.sh,
                        systemd units
scripts/                mac_reporter.py (Mac HTTP endpoint the Pi polls), panel_qa.py +
                        PANEL-INTAKE.md (per panel intake), spin_demo.py, gen_tracker.py,
                        smoke_test.py, show_white.py, pico_colorimeter.py, WB-PROCEDURE.md
qa_preview/             271 rendered QA patterns
qa/QA-SHEET.md          Per panel results. Empty; no panel has been tested.
PARTS.md                Shopping list. Prices checked 2026-08-19.
PARTS-TRACKER.xlsx      What was actually ordered, and what it cost
config.example.toml     Copy to config.toml
deploy.sh               rsync to the Pi, with --bootstrap for the first run
```

## What is not built

Stated plainly, because the value of everything above depends on this list being complete.

- **No panel has been driven.** The ten panels have arrived and the Pi runs the whole software
  stack, but the bonnet and the 5V supplies have not landed, so nothing in this repository has lit
  an LED.
- **The PCB is routed but not signed off.** The last design rule check finds no violations and no
  unrouted signal, but it still reports 7 ground pour islands, which is the one defect that matters
  most on a board whose power design assumes a continuous return. Gerbers exist; stitch the ground
  first. The board is also still parked: the build uses the bonnet and bus bar path.
- **Neither iOS app's now playing path is verifiable off a phone.** They build and run on device,
  but the simulator stubs MediaPlayer, so that path is only ever exercised on real hardware.
- **No panel has been through intake QA.** The patterns and the procedure exist; the results sheet
  is an empty table.
- **The renderer's output has never reached an LED.** It compiles and runs on the Pi, but with no
  panel attached everything it maps goes into the library and stops there.
- **No streaming account is linked yet.** The Spotify, Last.fm and ListenBrainz
  adapters are written, but every credential in `config.toml` is still empty, so none of them has
  answered live. Only Apple Music (phone push, Music.app, account view) and the Mac's own Now
  Playing have.
- **Nothing on an iPhone other than Apple Music can be read by an app.** iOS gives an app only the
  Music player; Spotify, Tidal and Deezer reach the wall through their own accounts (Spotify's
  API, or Last.fm), and SoundCloud, YouTube Music and Amazon Music reach it only from a Mac or
  out loud.
- **Panel performance is unmeasured.** The software side is measured (`scripts/bench_frames.py`
  bounds the producer, the brain prints its sustained fps, and the 60 Hz map cap came out of a
  measured black-flashing regression), but refresh on real LEDs, CPU under a real load, and power
  draw are not. The 9600 Hz figure in the source comments is the panel library's specification,
  not a result from this room.
- **History is a journal, not a database.** Plays land in `journal.jsonl` (capped at 500, replay
  by timestamp); there is no search and no analytics on the brain side.
- **Every app is unproven against a wall.** Web, AlbumWall and Tessera all drive
  `brain/control.py`, and that API has run on the real Pi, but the loop from app to brain to lit
  panel has never been closed.
- **The web app's push-to-wall has not touched the Pi.** Its "Pi brain" push format matches
  `brain/control.py`'s `/frame` contract byte for byte, and the CORS headers that let a browser call
  that API are committed here, but the Pi was offline when this landed, so the loop web → brain →
  panel has never been closed. The Apple Music bridge path, by contrast, was verified live.
- **The white balance gains are unmeasured**, and labelled as such in the config.
- **No automated tests.** `scripts/smoke_test.py` is a visual check that writes PNGs for a human to
  look at, plus one assertion on frame size. There is no test runner and no CI.

---

Jalen Edusei, [jalenedusei.com](https://www.jalenedusei.com),
[github.com/jke48222](https://github.com/jke48222)

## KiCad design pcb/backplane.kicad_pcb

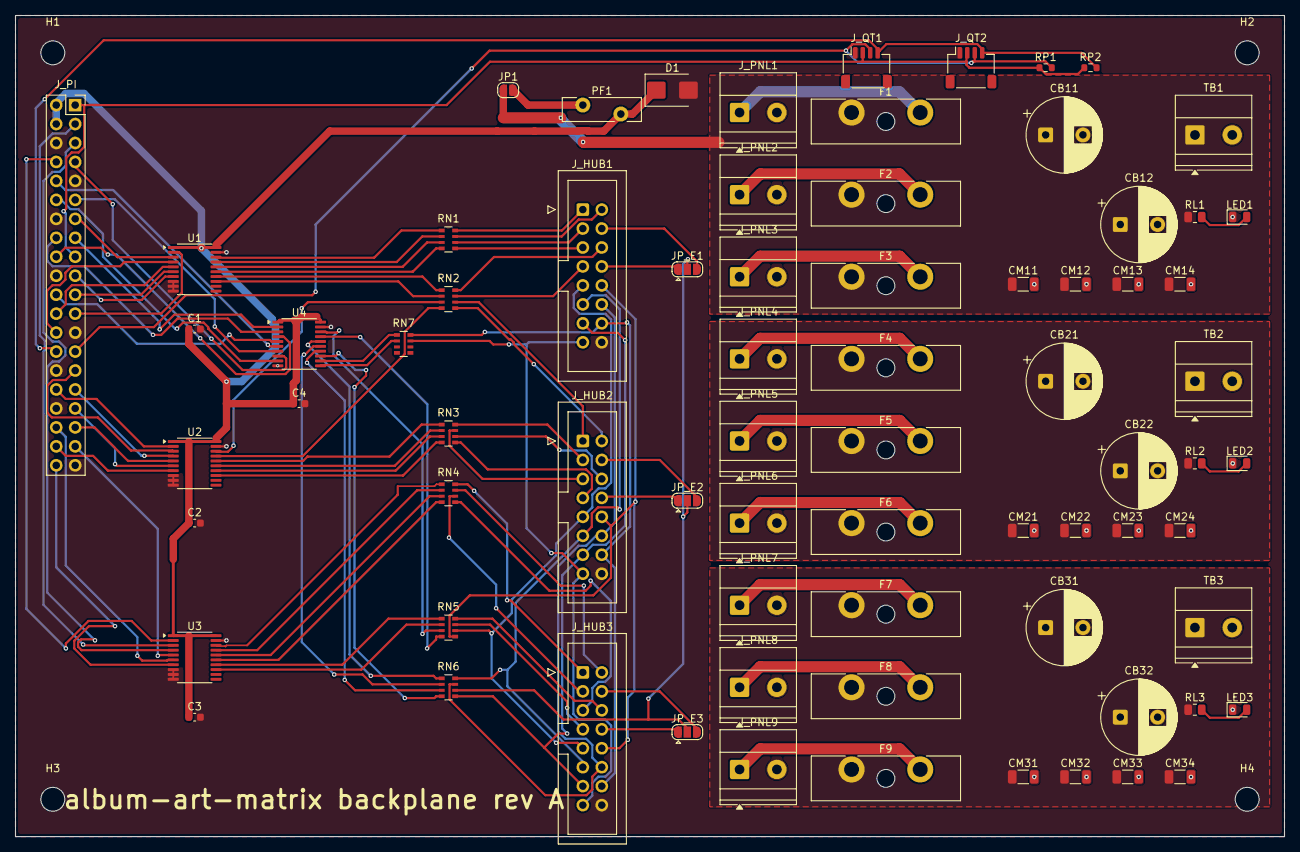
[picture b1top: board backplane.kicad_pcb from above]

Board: 2 copper layers, 170.0 x 110.0 mm, 78 parts (0 on the bottom side), 105 nets.

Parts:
C1, C2, C3, C4: 100nF; C_0603_1608Metric
CB11, CB12, CB21, CB22, CB31, CB32: 1000uF_10V; CP_Radial_D10.0mm_P5.00mm
CM11, CM12, CM13, CM14, CM21, CM22, CM23, CM24, CM31, CM32, CM33, CM34: 22uF_10V; C_1206_3216Metric
D1: SMBJ5.0A; D_SMB
F1, F2, F3, F4, F5, F6, F7, F8, F9: ATO_FUSE_10A; Fuseholder_Blade_ATO_Littelfuse_Pudenz_2_Pin
H1, H2, H3, H4: M3; MountingHole_3.2mm_M3
JP1: PI_PWR_EN; SolderJumper-2_P1.3mm_Open_RoundedPad1.0x1.5mm
JP_E1, JP_E2, JP_E3: E_PIN8_or_PIN4; SolderJumper-3_P1.3mm_Open_RoundedPad1.0x1.5mm
J_HUB1, J_HUB2, J_HUB3: HUB75_IDC_2x8; IDC-Header_2x08_P2.54mm_Vertical
J_PI: PI5_GPIO_2x20; PinSocket_2x20_P2.54mm_Vertical
J_PNL1, J_PNL2, J_PNL3, J_PNL4, J_PNL5, J_PNL6, J_PNL7, J_PNL8, J_PNL9: PANEL_5V_OUT; TerminalBlock_Phoenix_MKDS-1,5-2_1x02_P5.00mm_Horizontal
J_QT1, J_QT2: STEMMAQT_I2C0; JST_SH_SM04B-SRSS-TB_1x04-1MP_P1.00mm_Horizontal
LED1, LED2, LED3: PWR_GREEN; LED_0805_2012Metric
PF1: POLYFUSE_5A; Fuse_Bourns_MF-RG500
RL1, RL2, RL3: 1k; R_0805_2012Metric
RN1, RN2, RN3, RN4, RN5, RN6, RN7: 33Rx4; R_Array_Convex_4x0603
RP1, RP2: 10k; R_0603_1608Metric
TB1, TB2, TB3: TRUNK_IN_12A; TerminalBlock_Phoenix_MKDS-1,5-2_1x02_P5.00mm_Horizontal
U1, U2, U3, U4: 74AHCT245PW; TSSOP-20_4.4x6.5mm_P0.65mm

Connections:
3V3: J_PI.1, J_PI.17, J_QT1.2, J_QT2.2, RP1.1, RP2.1
GND: C1.2, C2.2, C3.2, C4.2, CB11.2, CB12.2, CB21.2, CB22.2, CB31.2, CB32.2, CM11.2, CM12.2, CM13.2, CM14.2, CM21.2, CM22.2, CM23.2, CM24.2, CM31.2, CM32.2, CM33.2, CM34.2, D1.2, J_HUB1.16, J_HUB2.16, J_HUB3.16, J_PI.6, J_PI.9, J_PI.14, J_PI.20, J_PI.25, J_PI.30, J_PI.34, J_PI.39, J_PNL1.2, J_PNL2.2, J_PNL3.2, J_PNL4.2, J_PNL5.2, J_PNL6.2, J_PNL7.2, J_PNL8.2, J_PNL9.2, J_QT1.1, J_QT2.1, LED1.1, LED2.1, LED3.1, TB1.2, TB2.2, TB3.2, U1.8, U1.9, U1.10, U1.19, U2.8, U2.9, U2.10, U2.19, U3.8, U3.9, U3.10, U3.19, U4.10, U4.19
GPIO2: J_PI.3, U3.3
GPIO3: J_PI.5, U3.4
GPIO4: J_PI.7, U4.8
GPIO5: J_PI.29, U2.3
GPIO6: J_PI.31, U2.4
GPIO7: J_PI.26, U1.4
GPIO8: J_PI.24, U1.5
GPIO9: J_PI.21, U1.6
GPIO10: J_PI.19, U1.7
GPIO11: J_PI.23, U1.2
GPIO12: J_PI.32, U2.2
GPIO13: J_PI.33, U2.6
GPIO14: J_PI.8, U3.2
GPIO15: J_PI.10, U4.6
GPIO16: J_PI.36, U3.6
GPIO17: J_PI.11, U4.7
GPIO18: J_PI.12, U4.9
GPIO19: J_PI.35, U2.5
GPIO20: J_PI.38, U2.7
GPIO21: J_PI.40, U3.7
GPIO22: J_PI.15, U4.2
GPIO23: J_PI.16, U4.3
GPIO24: J_PI.18, U4.4
GPIO25: J_PI.22, U4.5
GPIO26: J_PI.37, U3.5
GPIO27: J_PI.13, U1.3
H1_B1: J_HUB1.3, RN1.6
H1_B1_D: RN1.3, U1.16
H1_B2: J_HUB1.7, RN2.7
H1_B2_D: RN2.2, U1.13
H1_E4: JP_E1.3, J_HUB1.4
H1_E8: JP_E1.1, J_HUB1.8
H1_G1: J_HUB1.2, RN1.7
H1_G1_D: RN1.2, U1.17
H1_G2: J_HUB1.6, RN2.8
H1_G2_D: RN2.1, U1.14
H1_R1: J_HUB1.1, RN1.8
H1_R1_D: RN1.1, U1.18
H1_R2: J_HUB1.5, RN1.5
H1_R2_D: RN1.4, U1.15
H2_B1: J_HUB2.3, RN3.8
H2_B1_D: RN3.1, U2.16
H2_B2: J_HUB2.7, RN3.5
H2_B2_D: RN3.4, U2.13
H2_E4: JP_E2.3, J_HUB2.4
H2_E8: JP_E2.1, J_HUB2.8
H2_G1: J_HUB2.2, RN2.5
H2_G1_D: RN2.4, U2.17
H2_G2: J_HUB2.6, RN3.6
H2_G2_D: RN3.3, U2.14
H2_R1: J_HUB2.1, RN2.6
H2_R1_D: RN2.3, U2.18
H2_R2: J_HUB2.5, RN3.7
H2_R2_D: RN3.2, U2.15
H3_B1: J_HUB3.3, RN4.6
H3_B1_D: RN4.3, U3.16
H3_B2: J_HUB3.7, RN5.7
H3_B2_D: RN5.2, U3.13
H3_E4: JP_E3.3, J_HUB3.4
H3_E8: JP_E3.1, J_HUB3.8
H3_G1: J_HUB3.2, RN4.7
H3_G1_D: RN4.2, U3.17
H3_G2: J_HUB3.6, RN5.8
H3_G2_D: RN5.1, U3.14
H3_R1: J_HUB3.1, RN4.8
H3_R1_D: RN4.1, U3.18
H3_R2: J_HUB3.5, RN4.5
H3_R2_D: RN4.4, U3.15
LEDA1: LED1.2, RL1.2
LEDA2: LED2.2, RL2.2
LEDA3: LED3.2, RL3.2
PIPWR_F: JP1.2, PF1.1
SCL0: J_PI.28, J_QT1.4, J_QT2.4, RP2.2
SDA0: J_PI.27, J_QT1.3, J_QT2.3, RP1.2
SH_A: J_HUB1.9, J_HUB2.9, J_HUB3.9, RN5.6
SH_A_D: RN5.3, U4.18
SH_B: J_HUB1.10, J_HUB2.10, J_HUB3.10, RN5.5
SH_B_D: RN5.4, U4.17
SH_C: J_HUB1.11, J_HUB2.11, J_HUB3.11, RN6.8
SH_CLK: J_HUB1.13, J_HUB2.13, J_HUB3.13, RN6.5
SH_CLK_D: RN6.4, U4.13
SH_C_D: RN6.1, U4.16
SH_D: J_HUB1.12, J_HUB2.12, J_HUB3.12, RN6.7
SH_D_D: RN6.2, U4.15
SH_E: JP_E1.2, JP_E2.2, JP_E3.2, RN6.6
SH_E_D: RN6.3, U4.14
SH_LAT: J_HUB1.14, J_HUB2.14, J_HUB3.14, RN7.8
SH_LAT_D: RN7.1, U4.12
SH_OE: J_HUB1.15, J_HUB2.15, J_HUB3.15, RN7.7
SH_OE_D: RN7.2, U4.11
V5_PI: C1.1, C2.1, C3.1, C4.1, D1.1, J_PI.2, J_PI.4, PF1.2, U1.1, U1.20, U2.1, U2.20, U3.1, U3.20, U4.1, U4.20
VF1: F1.2, J_PNL1.1
VF2: F2.2, J_PNL2.1
VF3: F3.2, J_PNL3.1
VF4: F4.2, J_PNL4.1
VF5: F5.2, J_PNL5.1
VF6: F6.2, J_PNL6.1
VF7: F7.2, J_PNL7.1
VF8: F8.2, J_PNL8.1
VF9: F9.2, J_PNL9.1
VP1: CB11.1, CB12.1, CM11.1, CM12.1, CM13.1, CM14.1, F1.1, F2.1, F3.1, JP1.1, RL1.1, TB1.1
VP2: CB21.1, CB22.1, CM21.1, CM22.1, CM23.1, CM24.1, F4.1, F5.1, F6.1, RL2.1, TB2.1
VP3: CB31.1, CB32.1, CM31.1, CM32.1, CM33.1, CM34.1, F7.1, F8.1, F9.1, RL3.1, TB3.1
